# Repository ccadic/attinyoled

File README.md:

# attinyoled
OLED and ATTINY85 PCB kicad project

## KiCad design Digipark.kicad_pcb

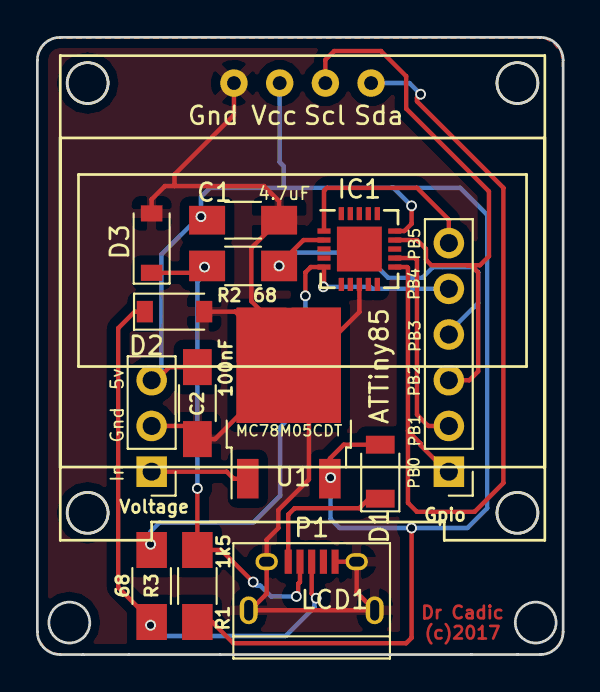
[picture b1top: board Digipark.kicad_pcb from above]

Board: 2 copper layers, 29.2 x 34.3 mm, 14 parts (0 on the bottom side), 12 nets.

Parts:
C1: 4.7uF; C_1206_HandSoldering
C2: 100nF; C_1206_HandSoldering
D1: D_Small; D_1206
D2, D3: Zener_MBR0520LT; D_SOD-123
Gpio: GPIOs; Socket_Strip_Straight_1x06_Pitch2.54mm
IC1: ATTINY85-M; QFN-20-1EP_4x4mm_Pitch0.5mm
LCD1: Oled96
P1: USB_OTG; USB_Micro-B
R1: 1k5; R_1206_HandSoldering
R2, R3: 68; R_1206_HandSoldering
U1: MC78M05CDT; TO-252-2
Voltage: Voltage; Socket_Strip_Straight_1x03_Pitch2.54mm

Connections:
+5V: C1.1, C2.1, D1.2, IC1.15, LCD1.3, R1.2, U1.3, Voltage.3
GND: C1.2, C2.2, D2.2, D3.2, IC1.8, LCD1.4, P1.5, P1.6, U1.2, Voltage.2
unnamed: D1.1, P1.1
unnamed: D2.1, P1.3, R3.2
unnamed: D3.1, P1.2, R1.1, R2.2
unnamed: Gpio.6, IC1.1
unnamed: Gpio.4, IC1.2, R2.1
unnamed: Gpio.5, IC1.5, R3.1
unnamed: Gpio.2, IC1.12
unnamed: U1.1, Voltage.1
SCL: IC1.14, LCD1.2
SDA: IC1.11, LCD1.1

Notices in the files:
Digipark.kicad_pcb:
(c)2017
